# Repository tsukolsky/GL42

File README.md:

GL42
====
This is the MI-Groves Growlight42 board.

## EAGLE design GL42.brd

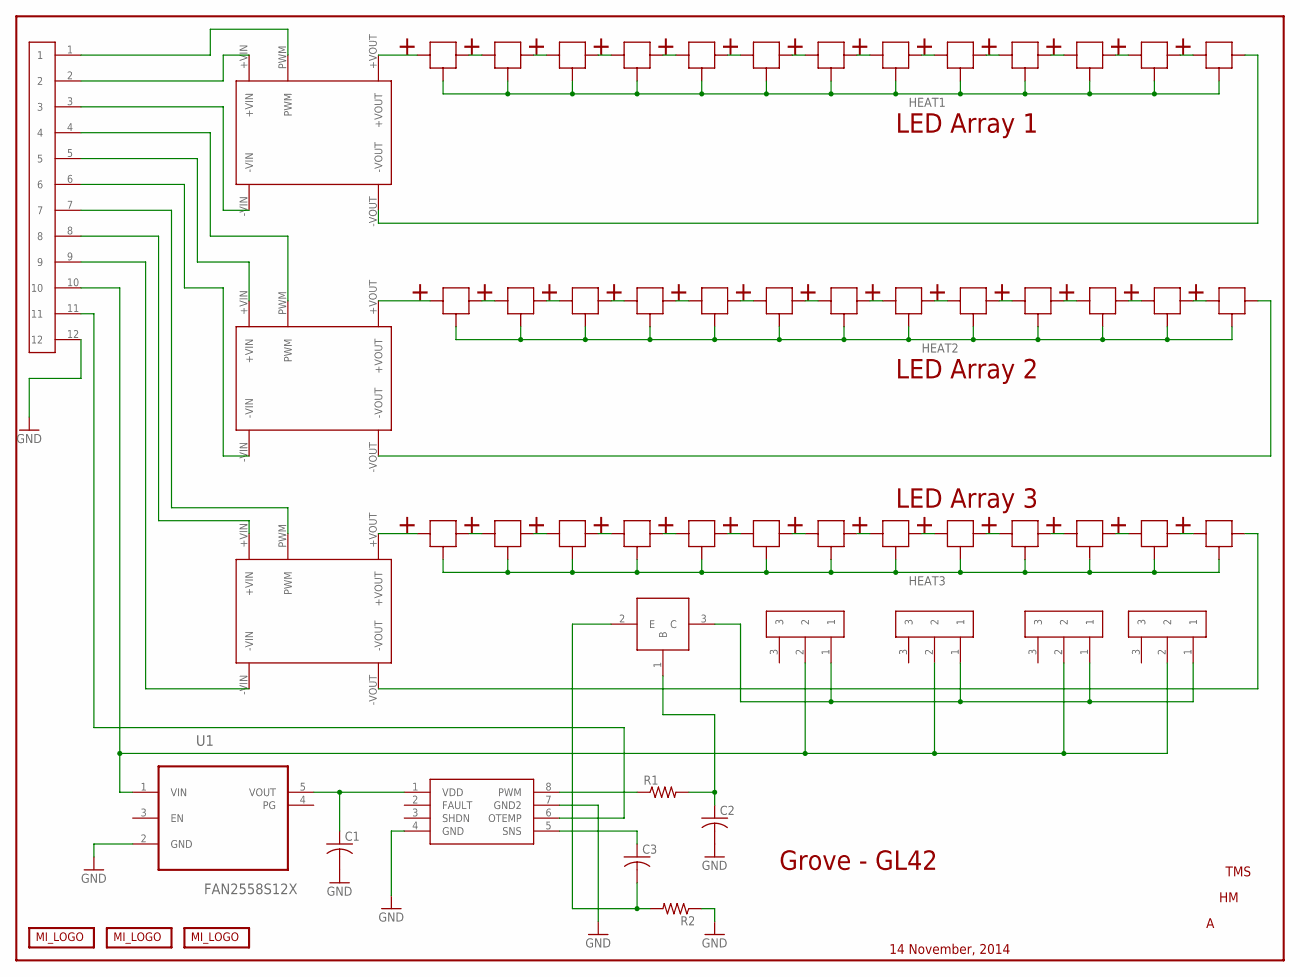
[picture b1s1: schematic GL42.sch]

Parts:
C1, C2, C3: C-USC1206; C1206
R1: R-US_R1206; R1206
R2: R-US_R2512; R2512
U1: FAN2558S12X; SOT95P280X145-5N
U$1, U$2, U$3, U$4, U$5, U$6, U$7, U$8, U$9, U$10, U$11, U$12, U$13, U$19, U$20, U$21, U$22, U$23, U$24, U$25, U$26, U$27, U$28, U$29, U$30, U$31, U$32, U$33, U$34, U$35, U$36, U$37, U$38, U$39, U$40, U$41, U$42, U$43, U$44: CREE_XP; XP
U$14: TC652; MSOP8
U$15: PH14SMT
U$16, U$17, U$18: LDD_HSMT
U$45: NPN_POWERTRAN; TO252
U$46, U$47, U$48, U$49: PH3SMT
U$50: MI_LOGO-GROVE; GROVES_LOGO
U$51: MI_LOGO-NAME_TWO; MI_LOGO_NAME_2
U$54: MI_LOGO-2014_USA; MACRIS_USA_LOGO

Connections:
GND: C1.2, C2.2, R2.1, U1.2 (GND), U$14.4 (GND), U$14.7 (GND2), U$15.12
HEAT1: U$1.THERMAL, U$2.THERMAL, U$3.THERMAL, U$4.THERMAL, U$5.THERMAL, U$6.THERMAL, U$7.THERMAL, U$8.THERMAL, U$9.THERMAL, U$10.THERMAL, U$11.THERMAL, U$12.THERMAL, U$13.THERMAL
HEAT2: U$19.THERMAL, U$20.THERMAL, U$21.THERMAL, U$22.THERMAL, U$23.THERMAL, U$24.THERMAL, U$25.THERMAL, U$26.THERMAL, U$27.THERMAL, U$28.THERMAL, U$29.THERMAL, U$30.THERMAL, U$31.THERMAL
HEAT3: U$32.THERMAL, U$33.THERMAL, U$34.THERMAL, U$35.THERMAL, U$36.THERMAL, U$37.THERMAL, U$38.THERMAL, U$39.THERMAL, U$40.THERMAL, U$41.THERMAL, U$42.THERMAL, U$43.THERMAL, U$44.THERMAL
unnamed: U$1.NEGATIVE, U$1.NEGATIVE1 (NEGATIVE), U$2.POSITIVE, U$2.POSITIVE1 (POSITIVE)
unnamed: U$2.NEGATIVE, U$2.NEGATIVE1 (NEGATIVE), U$3.POSITIVE, U$3.POSITIVE1 (POSITIVE)
unnamed: U$3.NEGATIVE, U$3.NEGATIVE1 (NEGATIVE), U$4.POSITIVE, U$4.POSITIVE1 (POSITIVE)
unnamed: U$4.NEGATIVE, U$4.NEGATIVE1 (NEGATIVE), U$5.POSITIVE, U$5.POSITIVE1 (POSITIVE)
unnamed: U$5.NEGATIVE, U$5.NEGATIVE1 (NEGATIVE), U$6.POSITIVE, U$6.POSITIVE1 (POSITIVE)
unnamed: U$6.NEGATIVE, U$6.NEGATIVE1 (NEGATIVE), U$7.POSITIVE, U$7.POSITIVE1 (POSITIVE)
unnamed: U$7.NEGATIVE, U$7.NEGATIVE1 (NEGATIVE), U$8.POSITIVE, U$8.POSITIVE1 (POSITIVE)
unnamed: U$8.NEGATIVE, U$8.NEGATIVE1 (NEGATIVE), U$9.POSITIVE, U$9.POSITIVE1 (POSITIVE)
unnamed: U$9.NEGATIVE, U$9.NEGATIVE1 (NEGATIVE), U$10.POSITIVE, U$10.POSITIVE1 (POSITIVE)
unnamed: U$10.NEGATIVE, U$10.NEGATIVE1 (NEGATIVE), U$11.POSITIVE, U$11.POSITIVE1 (POSITIVE)
unnamed: U$11.NEGATIVE, U$11.NEGATIVE1 (NEGATIVE), U$12.POSITIVE, U$12.POSITIVE1 (POSITIVE)
unnamed: U$12.NEGATIVE, U$12.NEGATIVE1 (NEGATIVE), U$13.POSITIVE, U$13.POSITIVE1 (POSITIVE)
unnamed: U$13.NEGATIVE, U$13.NEGATIVE1 (NEGATIVE), U$16.-VOUT
unnamed: U$15.1, U$16.PWM
unnamed: U$15.2, U$16.+VIN
unnamed: U$15.3, U$16.-VIN
unnamed: U$1.POSITIVE, U$1.POSITIVE1 (POSITIVE), U$16.+VOUT
unnamed: C2.1, R1.2, U$45.1 (B)
unnamed: U$15.4, U$17.PWM
unnamed: U$15.5, U$17.+VIN
unnamed: U$15.6, U$17.-VIN
unnamed: U$15.7, U$18.PWM
unnamed: U$15.8, U$18.+VIN
unnamed: U$15.9, U$18.-VIN
unnamed: U$17.+VOUT, U$19.POSITIVE, U$19.POSITIVE1 (POSITIVE)
unnamed: U$19.NEGATIVE, U$19.NEGATIVE1 (NEGATIVE), U$20.POSITIVE, U$20.POSITIVE1 (POSITIVE)
unnamed: U$20.NEGATIVE, U$20.NEGATIVE1 (NEGATIVE), U$21.POSITIVE, U$21.POSITIVE1 (POSITIVE)
unnamed: U$21.NEGATIVE, U$21.NEGATIVE1 (NEGATIVE), U$22.POSITIVE, U$22.POSITIVE1 (POSITIVE)
unnamed: U$22.NEGATIVE, U$22.NEGATIVE1 (NEGATIVE), U$23.POSITIVE, U$23.POSITIVE1 (POSITIVE)
unnamed: U$23.NEGATIVE, U$23.NEGATIVE1 (NEGATIVE), U$24.POSITIVE, U$24.POSITIVE1 (POSITIVE)
unnamed: U$24.NEGATIVE, U$24.NEGATIVE1 (NEGATIVE), U$25.POSITIVE, U$25.POSITIVE1 (POSITIVE)
unnamed: U$25.NEGATIVE, U$25.NEGATIVE1 (NEGATIVE), U$26.POSITIVE, U$26.POSITIVE1 (POSITIVE)
unnamed: U$26.NEGATIVE, U$26.NEGATIVE1 (NEGATIVE), U$27.POSITIVE, U$27.POSITIVE1 (POSITIVE)
unnamed: U$27.NEGATIVE, U$27.NEGATIVE1 (NEGATIVE), U$28.POSITIVE, U$28.POSITIVE1 (POSITIVE)
unnamed: U$28.NEGATIVE, U$28.NEGATIVE1 (NEGATIVE), U$29.POSITIVE, U$29.POSITIVE1 (POSITIVE)
unnamed: U$29.NEGATIVE, U$29.NEGATIVE1 (NEGATIVE), U$30.POSITIVE, U$30.POSITIVE1 (POSITIVE)
unnamed: U$30.NEGATIVE, U$30.NEGATIVE1 (NEGATIVE), U$31.POSITIVE, U$31.POSITIVE1 (POSITIVE)
unnamed: U$17.-VOUT, U$31.NEGATIVE, U$31.NEGATIVE1 (NEGATIVE)
unnamed: U$18.+VOUT, U$32.POSITIVE, U$32.POSITIVE1 (POSITIVE)
unnamed: U$32.NEGATIVE, U$32.NEGATIVE1 (NEGATIVE), U$33.POSITIVE, U$33.POSITIVE1 (POSITIVE)
unnamed: U$33.NEGATIVE, U$33.NEGATIVE1 (NEGATIVE), U$34.POSITIVE, U$34.POSITIVE1 (POSITIVE)
unnamed: U$34.NEGATIVE, U$34.NEGATIVE1 (NEGATIVE), U$35.POSITIVE, U$35.POSITIVE1 (POSITIVE)
unnamed: U$35.NEGATIVE, U$35.NEGATIVE1 (NEGATIVE), U$36.POSITIVE, U$36.POSITIVE1 (POSITIVE)
unnamed: U$36.NEGATIVE, U$36.NEGATIVE1 (NEGATIVE), U$37.POSITIVE, U$37.POSITIVE1 (POSITIVE)
unnamed: U$37.NEGATIVE, U$37.NEGATIVE1 (NEGATIVE), U$38.POSITIVE, U$38.POSITIVE1 (POSITIVE)
unnamed: U$38.NEGATIVE, U$38.NEGATIVE1 (NEGATIVE), U$39.POSITIVE, U$39.POSITIVE1 (POSITIVE)
unnamed: U$39.NEGATIVE, U$39.NEGATIVE1 (NEGATIVE), U$40.POSITIVE, U$40.POSITIVE1 (POSITIVE)
unnamed: U$40.NEGATIVE, U$40.NEGATIVE1 (NEGATIVE), U$41.POSITIVE, U$41.POSITIVE1 (POSITIVE)
unnamed: U$41.NEGATIVE, U$41.NEGATIVE1 (NEGATIVE), U$42.POSITIVE, U$42.POSITIVE1 (POSITIVE)
unnamed: U$42.NEGATIVE, U$42.NEGATIVE1 (NEGATIVE), U$43.POSITIVE, U$43.POSITIVE1 (POSITIVE)
unnamed: U$43.NEGATIVE, U$43.NEGATIVE1 (NEGATIVE), U$44.POSITIVE, U$44.POSITIVE1 (POSITIVE)
unnamed: U$18.-VOUT, U$44.NEGATIVE, U$44.NEGATIVE1 (NEGATIVE)
unnamed: C1.1, U1.5 (VOUT), U$14.1 (VDD)
unnamed: R1.1, U$14.8 (PWM)
unnamed: C3.2, R2.2, U$45.2 (E)
unnamed: U$14.6 (OTEMP), U$15.11
unnamed: U1.1 (VIN), U$15.10, U$46.2, U$47.2, U$48.2, U$49.2
unnamed: C3.1, U$14.5 (SNS)
unnamed: U$45.3 (C), U$46.1, U$47.1, U$48.1, U$49.1

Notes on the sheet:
Grove - GL42
TMS
14 November, 2014
LED Array 1
LED Array 2
LED Array 3

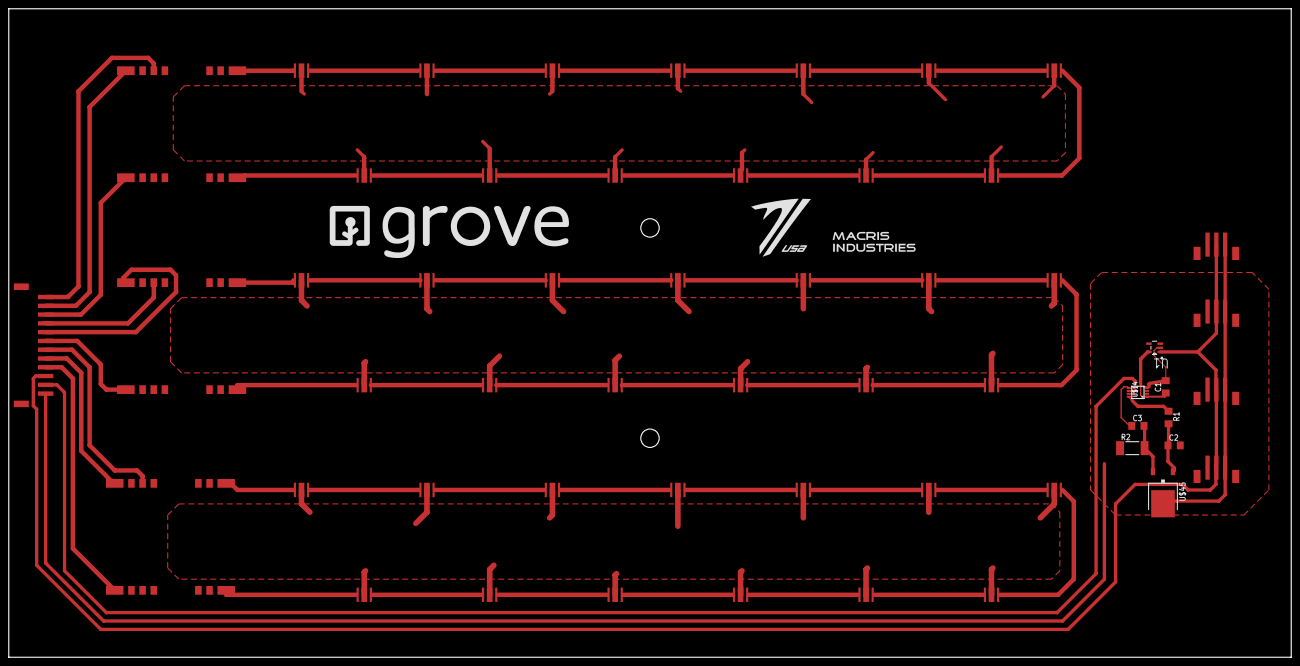
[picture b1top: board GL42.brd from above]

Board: 2 copper layers, 292.1 x 147.7 mm, 60 parts (0 on the bottom side), 63 nets.

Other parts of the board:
U$52, U$53: FOOT#8
